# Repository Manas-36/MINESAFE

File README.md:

<div align="center">

**Integrated Worker Safety and Health Monitoring System for Mining Operations**<br>
Capstone project · B.E. Mechanical and Mechatronics Engineering · Thakur College of Engineering and Technology (TCET), Mumbai · 2026–27

</div>

MineSafe checks a miner's safety kit at the gate, watches their health and movement underground, shows where they are on a tunnel map, and lets the control room warn everyone in seconds — **without GPS, internet or cabling**.

---

## The problem

In 2024 DGMS recorded **38 fatal accidents in Indian coal mines and 32 in metalliferous mines**; fall of ground, fall of person and powered haulage lead the list. Underground there is no GPS and no mobile network. The control room cannot see a worker's condition or position, kit checks at the gate are manual, and gas, falls and heat stress are usually discovered after the fact. Existing tools each solve one piece (gas detectors, RFID gates, smart helmets, CCTV PPE detection); our [competitive analysis of nine commercial products](docs/research/competitors.md) found none that combines AI kit compliance, continuous health monitoring and GPS-free location in one underground system.

## How it works

```mermaid
flowchart LR
  B["Body unit<br>worn by miner"] -->|ESP-NOW| R3["REP-03<br>2 hops"]
  R3 -->|ESP-NOW| R2["REP-02<br>1 hop"]
  R2 -->|ESP-NOW| R1["REP-01 main<br>hop 0"]
  R1 -->|"Wi-Fi HTTP every 1 s"| H["Admin hub (laptop)<br>Flask + AI + map + gas"]
  P["Phone camera<br>entry photo"] -->|Wi-Fi| H
  E["Entry station<br>RFID gear tags"] -->|Wi-Fi| H
  H -.->|"alert in reply"| R1
  R1 -.->|beacons| R2
  R2 -.->|beacons| R3
  R3 -.->|"beacons → LED"| B
```

| Part | What it does |
|---|---|
| **Entry station** | XIAO ESP32-S3 Sense: RFID (NTAG215) tags on helmet, vest, pants, shoes + **built-in camera photo** (PHOTO button) + AI kit check (YOLOv8). Admin approves and pairs a body unit. Phone photo page as backup. |
| **Body unit** | ESP32-S3 N16R8 with MPU6050, BMP180, DS18B20, MAX30100/30102 (an ESP32-C6 + MPU6050 "mock" unit adds a second worker for demos). Steps, heading, fall, no movement, body temp, heart rate, SpO₂ (estimate), height, SOS button, alert LED. |
| **Repeater chain** | XIAO ESP32-C6 nodes along the tunnel relay data hop by hop over ESP-NOW. Routes form and heal by themselves. Each node has a buzzer and an MQ gas sensor. |
| **Control room** | `admin_hub.py` on a laptop: live status, tunnel map with worker dots, gas & air, worker registration with medical card, entry check, AI kit check, network health, incident log, one-click alert. |

### Location without GPS
Raw double integration of acceleration drifts by ~175 m in a minute, so MineSafe uses **pedestrian dead reckoning**: steps × step length along the gyro heading, kept inside the tunnels drawn on the map, and reset every time the worker passes close to a repeater. Pressure from the BMP180 gives the level (z). A built-in **Demo walker** shows the drift correction with no hardware.

### Detection rules (all editable)
| Event | Rule |
|---|---|
| Fall | free fall < 0.4 g and/or impact > 3 g, then lying > 55° after 2 s |
| No movement | no motion for 30 s (demo setting) |
| Body temperature | warning ≥ 38 °C, danger ≥ 39.5 °C |
| Heart rate | warning < 50 / > 120 bpm, danger < 40 / > 150 bpm |
| SpO₂ (estimate) | warning ≤ 92 %, danger ≤ 88 % |
| Gas | a sensor's main gas reaches its danger ppm → automatic alert to everyone |

## Progress

### Current status (5 Oct 2026)

> **V3 is in calibration — not complete yet.** The software (hub, dashboard, map, alerts, gas + air) works with the simulator and the first hardware runs. We are now integrating and calibrating the sensors one board at a time:
>
> - **Body unit on the ESP32-C6-WROOM-1 DevKit** — own pin map in `body_node`; sensors checked with [`firmware/tests/body_sensor_test`](firmware/tests/body_sensor_test) (wire check + pin finder). Currently fixing the I²C / DS18B20 wiring.
> - **Scanning system (entry station) on an ESP32-C6** — PN532 RFID antenna + OLED + buttons, checked with [`firmware/tests/entry_hw_test`](firmware/tests/entry_hw_test); entry photo from the phone page. (The XIAO S3 Sense camera build is kept as an option.)
> - **Sensor code cross-checked** against the standard libraries and datasheets; [`firmware/tests/body_lib_test`](firmware/tests/body_lib_test) reads every body sensor with the well-known Arduino libraries.
> - **Repeaters (XIAO ESP32-C6)** — chain, buzzer, MQ gas and AHT air sensor working on the bench (31.3 °C / 62 % RH).
>
> **V4 — our own PCBs and sensor boards.** Once V3 is calibrated, the breadboard wiring is replaced by custom-designed PCBs: a compact body-unit board with the sensors on it, a repeater board and an entry-station board — see [docs/v4.md](docs/v4.md).

**Major versions:** [V1](docs/v1.md) Wi-Fi + cloud, no website → [V2](docs/v2.md) ESP-NOW chain + control-room website → **[V3](docs/v3.md) camera entry station + sensor integration (now, calibrating)** → **[V4](docs/v4.md) our own PCBs and sensor boards**

**42 / 59 tasks done · Week 9 of 14** `████████████████████░░░░░░░░░░` → full week-by-week plan, Gantt chart and checklist in **[ROADMAP.md](ROADMAP.md)**

| Version | Milestone | Status |
|---|---|---|
| v0.0 | Research, competitive analysis, architecture, pilot BOM | ✅ |
| v0.1 | Entry station reads / writes gear tags; tag registry | ✅ |
| v0.2 | Phone photo verification, body-unit clearance | ✅ |
| v0.3 | Control room v3: workers, live monitoring, alerts; entry station v2 | ✅ |
| v0.4 | Repeater chain, AI kit check, gas; Zigbee → ESP-NOW | ✅ |
| v0.5 | First end-to-end run: phone worker, body unit, alerts, buzzer | ✅ tested on hardware |
| v0.6 | Tunnel map + GPS-free tracking, gas analysis, real body sensors | ✅ software · 🔧 sensor bench test next |
| v1.0 | Structured repo, docs, presentation, Notion | ✅ |
| **V3 · v3.0** | Camera entry station (XIAO S3 Sense), mock worker, schematics, admin theme, research docs — [docs/v3.md](docs/v3.md) | ✅ software · 🔧 hardware test next |
| v3.1 | AHT air temperature + humidity on every repeater, shown in the admin with wet-bulb heat warnings | ✅ software · 🔧 hardware test next |
| v3.2 | Body unit on ESP32-C6-WROOM-1 DevKit, sensor + entry hardware test sketches, serial on both USB sockets | 🔧 calibrating sensors |
| v3.3 | Repeater exit sign (LED matrix) + evacuation routes to the nearest safe exit, 3 gas sensors per repeater, editable gas limits (CMR 2017 / NIOSH) — [gas limits](docs/gas_limits.md) · [final BOM](docs/final_bom.md) · [run guide](docs/run_on_laptop.md) | ✅ software · 🔧 hardware next |
| **V4** | Custom PCBs: body-unit sensor board, repeater board, entry-station board — [docs/v4.md](docs/v4.md) | 📋 planned |

Every version has its own branch (`version/v0.0` … `version/v1.0`) — see [CHANGELOG.md](CHANGELOG.md) for what changed and [docs/decisions.md](docs/decisions.md) for why.

## Repository layout

```
firmware/
  body_node/          body unit (worn)            – ESP32-S3 or XIAO ESP32-C6
  repeater_node/      main + tunnel repeaters     – set IS_GATEWAY / REPEATER_NO
  entry_station/      RFID gear tag station        – XIAO ESP32-C6 + PN532 + OLED
  tests/              i2c_scan, rc522_test, pn532_ntag215_test
hub/
  admin_hub.py        control room server + dashboard (Flask)
  requirements.txt
tools/
  sim_repeater.py     fake repeater chain + 3 workers (no hardware)
  mock_repeater.py    serves the repeater's phone test page on a PC
hardware/
  bom_prototype.csv   parts for the built prototype
  bom_pilot.csv       parts for the 20-worker pilot design
docs/
  v1.md v2.md v3.md  architecture.md  wiring.md  setup.md  protocol.md  decisions.md
  wiring/             schematics (SVG + PNG) and the script that draws them
  research/           literature review, competitor analysis, pilot design, original reports (source/)
  presentation/       slide outline (add the exported PDF here)
  images/             screenshots
CHANGELOG.md          version-by-version progress
ROADMAP.md            week-by-week plan and to-do list
```

## Quick start

1. **Hub (laptop)**
   ```bash
   cd hub
   pip install -r requirements.txt     # ultralytics is optional (AI kit check)
   python admin_hub.py                 # open http://localhost:5000
   ```
   No hardware yet? Run `python tools/sim_repeater.py` in a second window, or press **▶ Demo walker** on the Map tab.
2. **Firmware (Arduino IDE, ESP32 core 3.x)**
   - Copy `secrets.example.h` → `secrets.h` in `repeater_node/` and `entry_station/`, fill in your hotspot and laptop IP.
   - Board: *ESP32S3 Dev Module* or *XIAO_ESP32C6*, USB CDC On Boot: Enabled, Serial Monitor 115200.
   - Main repeater: `IS_GATEWAY 1`, `REPEATER_NO 1`. Tunnel repeaters: `IS_GATEWAY 0`, numbers 2, 3, 4 …
   - Body unit: set `BODY_ID`, stand still 3 s at power-on.
3. **Test with a phone:** join the hotspot, open `http://<repeater IP>/` — the phone acts as a worker (fall, SOS, walk on the map).

Full steps: [docs/setup.md](docs/setup.md) · Wiring + schematics: [docs/wiring.md](docs/wiring.md) · Packet format: [docs/protocol.md](docs/protocol.md) · Architecture: [docs/architecture.md](docs/architecture.md)

## Screenshots

**New (v3.5): MineSafe Control** — a 3D control-room app at `http://<laptop-ip>:5000/control/`, live data only, works on a phone: **[docs/control_app.md](docs/control_app.md)**.

Every page of the classic control-room website: **[docs/website.md](docs/website.md)**. Reports: **[docs/report](docs/report/)** (blue book + figures).

| Evacuation map | Live |
|---|---|
|  |  |
| **Gas limits** | **Body unit display (v3.4)** |
|  |  |

*Screens from a test run with the demo mine map, the repeater simulator and fictional demo workers.*

## Bill of materials

| Build | Cost |
|---|---|
| Prototype (1 body unit, 2 repeaters, entry station; laptop + phone owned) | ≈ ₹6,500 |
| Pilot design (20 workers, 2 entry chambers, 8 UWB/LoRa repeaters, gateway, server) | ≈ ₹3,01,000 |

Approximate India-market prices, 2026. Item-by-item: [hardware/bom_prototype.csv](hardware/bom_prototype.csv) · [hardware/bom_pilot.csv](hardware/bom_pilot.csv).

## Future scope
Zigbee (802.15.4) mesh on ESP32-C6 nodes · UWB anchors for sub-metre location · LoRa backbone for long tunnels · MQ-4 / electrochemical CO and O₂ sensors · intrinsically safe enclosure · kit-removal sensing (helmet IR sensor, vest buckle reed switch, BLE tags) · OLED messages to workers · shift analytics.

## Team
| Name | Roll no. | GitHub |
|---|---|---|
| Manas Pednekar | 36 | [@Manas-36](https://github.com/Manas-36) |
| Amey Satale | 46 | [@Ameyty](https://github.com/Ameyty) |
| Aaryaa Kanojia | 18 | [@aaryaakanojia21](https://github.com/aaryaakanojia21) |

Guide: **Mr Dipesh Tare**, Assistant Professor · Full credits: [CONTRIBUTORS.md](CONTRIBUTORS.md)

## Licence
MIT — see [LICENSE](LICENSE).

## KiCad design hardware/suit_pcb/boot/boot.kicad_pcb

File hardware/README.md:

# MineSafe hardware — repeater PCB v4.0 and case

> V4 smart suit pods (4 PCBs + enclosures + full-suit CAD): see **[suit.md](suit.md)**.

This replaces the breadboard / jumper-wire repeater with **one carrier PCB** for the Seeed XIAO ESP32-C6 and a **mine-rated enclosure** designed around it. It uses the same pins as `firmware/repeater_node` (v3.3), so the firmware runs unchanged. Set `GAS_CHANNELS 3` to use all three gas inputs.

| | |
|---|---|
|  |  |
|  |  |

## What a repeater has to survive underground — and how the design answers it
| Mine condition | Design answer |
|---|---|
| **Water**: roof drips, wet walls, hosing-down, humidity up to 100 % | Sealed base and lid: a 3 mm silicone cord in a groove on a 9 mm land, with a tongue on the lid that presses it (aim **IP65**). A **drip hood** over the window. Every opening that could collect water faces **down**: the power gland, the pressure vent, and the CO and H₂S ports. The side vent of the AHT20 chamber sits under a drip lip. Conformal-coat the PCB after testing. |
| **Dust** (coal and rock dust) | Same seal. Every sensor breathes only through a **sintered-bronze disc and an ePTFE membrane**, never through open holes. |
| **Methane, which is lighter than air**, collects at the roof | The **MQ-4 (CH₄)** port is in the **top** wall. It sits under a "chimney" with side windows, so gas gets in but drips cannot fall onto the membrane. |
| **H₂S, which is heavier than air**, and CO | The **MQ-136 (H₂S)** and **MQ-7 (CO)** ports are in the **bottom** wall. Short skirts protect them from knocks. |
| **Gas ignition risk** (hot MQ heaters, sparks) | Each sensor port has a seat for a **sintered flame-arrestor disc**. The sensor board screws onto a foam gasket, so the heater only "sees" the outside through that disc. ⚠ A real coal-mine product still needs intrinsic-safety design and certification (Ex ia / Ex d). This case is a capstone prototype and is **not certified**. |
| **Heat** (30–45 °C) plus the MQ heaters (≈ 0.75 W each) | The **AHT20 sits in its own walled chamber** in the bottom-left corner. It has its own vent, far from the heaters, so it measures the tunnel air and not the box. A switching regulator (K7805, ≈ 90 % efficient) replaces a hot linear 7805. |
| **Blasting shock and vibration** | All boards are on screw bosses, with no hot glue and no breadboard. The XIAO and the 74HCT125 sit in sockets with a cable-tie. JST-XH latching connectors are used throughout. The lid lugs have gussets, and the mounting tabs have ribs. Fit **rubber grommets** in the 16 mm mounting holes. |
| **Falling rock, knocks from machines** | 3.5–4 mm walls in PC-ABS FR. The window is **3 mm polycarbonate** set in a recess behind a raised bezel. The SOS button has a **guard ring** with finger gaps, so a passing load cannot press it but a gloved hand can. |
| **Mine power cuts** | Two inputs: **MAIN 9–30 V** (mine supply) and **BATT 12 V** (3S 18650 pack with BMS). They are joined through Schottky diodes, so the board switches to battery with no reset. A **mains-present signal** (Q2 → D7) lets the firmware report "running on battery". On the input: a 1.6 A slow fuse, a 36 V TVS and a 470 µF capacitor. |
| **Radio in a rock tunnel** | The XIAO's u.FL connector goes through a pigtail to an **SMA bulkhead on the top wall**, so the antenna sits outside the box and clear of the rock face. |
| **Visibility in smoke and darkness** | The LED-matrix exit sign is under the hood, at eye level when the box is mounted on the rib. Two recesses take **reflective hi-vis tape**, which shows up in cap-lamp light. A power LED shows through a light pipe. |
| **Mounting** on the rib, a rock-bolt plate, roof mesh or a chain | Top and bottom tabs with a 16 mm hole (grommet, bolt or hook) and two slots each. Hang the box with the top tab only from roof mesh, or bolt both tabs to the rib. |
| **Static electricity** | Use antistatic FR plastic. An **earth stud boss** inside bonds the box to the mine earth. |
| **Pressure and temperature swings** (ventilation fans, depth) | An M12 **ePTFE pressure vent** in the bottom wall stops the seal from "breathing" water in. |

## Wiring the prototype

Every cable from the PCB connectors to the parts in the case, pin by pin, with lengths and wire colours. Generated by `docs/wiring/make_repeater_v4_wiring.py`. Shopping list for two repeaters: [`repeater_x2_shopping_list.xlsx`](repeater_x2_shopping_list.xlsx).

## PCB — `repeater_pcb/`
- **Board**: 100 × 75 mm, 2 layers, 1.6 mm, ground pour on both layers. Every part is through-hole, so the team can hand-solder it. 4 × M3 holes, 3.5 mm in from each corner.
- **Circuit**: [schematic](repeater_pcb/renders/repeater_schematic.png).
  - **Power**: OR diodes → fuse → TVS → K7805-2000R3 (5 V / 2 A).
  - **Controller**: XIAO ESP32-C6 on sockets.
  - **Matrix driver**: a 74HCT125 lifts the 3.3 V signals to 5 V for the MAX7219.
  - **Gas inputs**: three MQ inputs, each with a 10 k / 20 k divider and a filter capacitor.
  - **Other parts**: buzzer driver (S8050 + flyback diode), SOS input with debounce, AHT20 header with I²C pull-ups.
- **Connectors**:
  - power terminals on the left;
  - MQ1–3 at the bottom;
  - matrix, buzzer, SOS and AHT20 on the right;
  - USB-C at the top for programming.
- **Routing**: autorouted with Freerouting. Power tracks are 0.8 mm, signal tracks 0.3 mm, clearance 0.25 mm. DRC shows 0 unconnected pads. The remaining DRC items are only silkscreen cosmetics and "footprint library not found" (no KiCad library table on the build machine).
- **Source files**: `build_board.py` generates the whole board (placement, netlist, DSN for Freerouting, SES import, zones and silkscreen). `repeater.kicad_pcb` / `.kicad_pro` open in KiCad 7+.
- **Parts list**: [`bom_pcb.csv`](repeater_pcb/bom_pcb.csv), about **₹730 per board** of parts plus about ₹60 for the bare PCB.

### Ordering the PCB (JLCPCB / PCBWay)
1. Upload `repeater_pcb/repeater_gerbers_jlcpcb.zip`.
2. Use the defaults: 2 layers, 1.6 mm, HASL (lead-free if you like), any colour. 5 boards cost about USD 2 plus shipping.
3. No assembly is needed. Solder the low parts first (resistors, diodes), then the sockets, connectors and capacitors.
4. Before fitting the XIAO, power J1 from 12 V. Check for 5.0 V at the U2B "5V" pin and 0 V between the XIAO pins. Then fit the XIAO.

## Case — `repeater_case/`
- **Two parts**: the **base**, which bolts to the wall and carries everything, and the **lid** (window, SOS button, buzzer grille, hood).
- **Outside size**: 223 × 292 × 118 mm, including the mounting tabs and the hood. The body alone is 198 × 228 × 84 mm.
- **Lid fixing**: 6 × M4 stainless screws into heat-set inserts in the base.
- **Files**:
  - `case_base.step/.stl`, `case_lid.step/.stl`;
  - `case_assembly.step`, which includes the PCB, matrix, sensors, battery and button as blocks for the fit check;
  - `build_case.py` (CadQuery), where every dimension is a named constant at the top.
- **Fit check**: `fit_report.txt`. The PCB, matrix, window, 3 MQ modules, AHT20, battery, charger, SOS button, buzzer, gland nut and vent nut clear the case and each other.

**Layout, front view with the lid off:**

| Zone | What sits there |
|---|---|
| Top wall | CH₄ chimney (right), SMA antenna (left) |
| Top of the lid | LED matrix behind the window, under the hood |
| Middle | PCB on 12 mm standoffs. Leave a USB-C service loop at the top. |
| Bottom row | AHT20 chamber with side vent · M16 power gland · battery bay (3S 18650 pack, BMS, charge module, strap slots) · CO and H₂S modules over their ports |
| Front of the lid, lower part | Buzzer grille · power LED · guarded 22 mm SOS button |

**Printing / making:**
- **Prototype**: FDM in **PETG or ASA**, 4 perimeters, 30 % infill. Print the base back-down and the lid face-down. You will need supports under the hood and the lugs.
- **Real use underground**: **PC-ABS FR, V-0 and antistatic** (surface resistance below 10⁹ Ω), injection-moulded or SLS-printed. Ordinary PLA softens at mine temperatures and is not flame-retardant.
- **Window**: 145 × 49 × 3 mm polycarbonate, laser-cut. Seal it with a 1 mm EPDM foam gasket or a bead of neutral-cure silicone.

### Extra parts for the case
| Part | Qty | ≈ ₹ |
|---|---|---|
| Silicone cord 3 mm (gasket), 1 m | 1 | 60 |
| M4 × 25 stainless screws + M4 heat-set inserts | 6 | 90 |
| M16 cable gland IP68 (for 6–10 mm cable) | 1 | 40 |
| M12 ePTFE pressure vent (screw-in) | 2 (bottom + AHT20 chamber) | 200 |
| Sintered bronze disc 25 mm × 3 mm (flame arrestor) | 3 | 180 |
| ePTFE membrane patches 25 mm (or cut from a vent sticker) | 4 | 120 |
| 22 mm IP67 mushroom push button (red, NO) | 1 | 150 |
| SMA bulkhead pigtail (u.FL → SMA female) + 2.4 GHz antenna | 1 | 250 |
| Polycarbonate sheet 3 mm, 150 × 50 | 1 | 60 |
| 3S 18650 pack with BMS (3 × 18650) + 12.6 V CC/CV buck-boost charge module | 1 | 900 |
| Reflective hi-vis tape 12 mm, 0.5 m | 1 | 50 |
| Rubber grommets 16 mm + M3 screws | — | 50 |
| Printing (PETG, ≈ 1.1 kg with supports) | — | 1,000 |
| **Case total** | | **≈ ₹3,150** |

With the PCB (≈ ₹790) and the modules already listed in [`docs/final_bom.md`](../docs/final_bom.md) (XIAO, matrix, MQ sensors, AHT20, buzzer), a complete repeater comes to about **₹6,000**.

## To do
- **Firmware**: read `MAINS_N` on D7 (GPIO17); LOW means mine supply present. Send an "on battery" flag in the status packet and show it on the hub and the 3D control app.
- **Battery charging**: the board does not charge the battery itself. The charge module in the battery bay takes VIN_MAIN and charges the 3S pack at 12.6 V CC/CV. Choose a buck-boost module so that it also works from a 12 V mine supply.
- **Before going underground**: water test (hose, 30 min), drop / impact test, and a 24 h run at 45 °C.

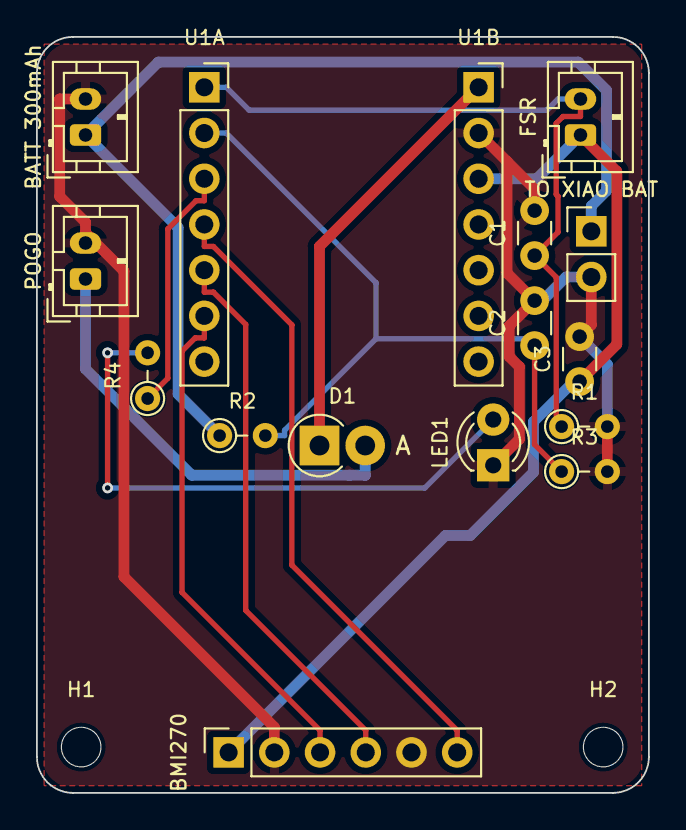
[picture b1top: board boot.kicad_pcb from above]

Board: 2 copper layers, 34.0 x 42.0 mm, 18 parts (0 on the bottom side), 12 nets.

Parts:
C1, C2, C3: 100nF; C_Disc_D3.0mm_W1.6mm_P2.50mm
D1: 1N5819; D_DO-41_SOD81_P2.54mm_Vertical_AnodeUp
H1, H2: M2; MountingHole_2.2mm_M2
J1: BATT 300mAh; JST_PH_B2B-PH-K_1x02_P2.00mm_Vertical
J2: POGO; JST_PH_B2B-PH-K_1x02_P2.00mm_Vertical
J3: FSR; JST_PH_B2B-PH-K_1x02_P2.00mm_Vertical
J4: TO XIAO BAT; PinHeader_1x02_P2.54mm_Vertical
LED1: STATUS; LED_D3.0mm
R1: 10k; R_Axial_DIN0204_L3.6mm_D1.6mm_P2.54mm_Vertical
R2, R3: 220k; R_Axial_DIN0204_L3.6mm_D1.6mm_P2.54mm_Vertical
R4: 1k; R_Axial_DIN0204_L3.6mm_D1.6mm_P2.54mm_Vertical
U1A: XIAO D0-D6; PinSocket_1x07_P2.54mm_Vertical
U1B: XIAO 5V-D7; PinSocket_1x07_P2.54mm_Vertical
U2: BMI270; PinSocket_1x06_P2.54mm_Vertical

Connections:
+3V3: C3.1, J3.1, U1B.3, U2.1
+5V: D1.1, U1B.1
BAT+: J1.1, J4.1, R2.1
FSR: C1.1, J3.2, R1.1, U1A.1
GND: C1.2, C2.2, C3.2, J1.2, J2.2, J4.2, LED1.1, R1.2, R3.2, U1B.2, U2.2, U2.5
IMU_INT: U1A.4, U2.6
LED: R4.1, U1A.3
LED_A: LED1.2, R4.2
POGO+: D1.2, J2.1
SCL: U1A.6, U2.3
SDA: U1A.5, U2.4
VBAT_SNS: C2.1, R2.2, R3.1, U1A.2

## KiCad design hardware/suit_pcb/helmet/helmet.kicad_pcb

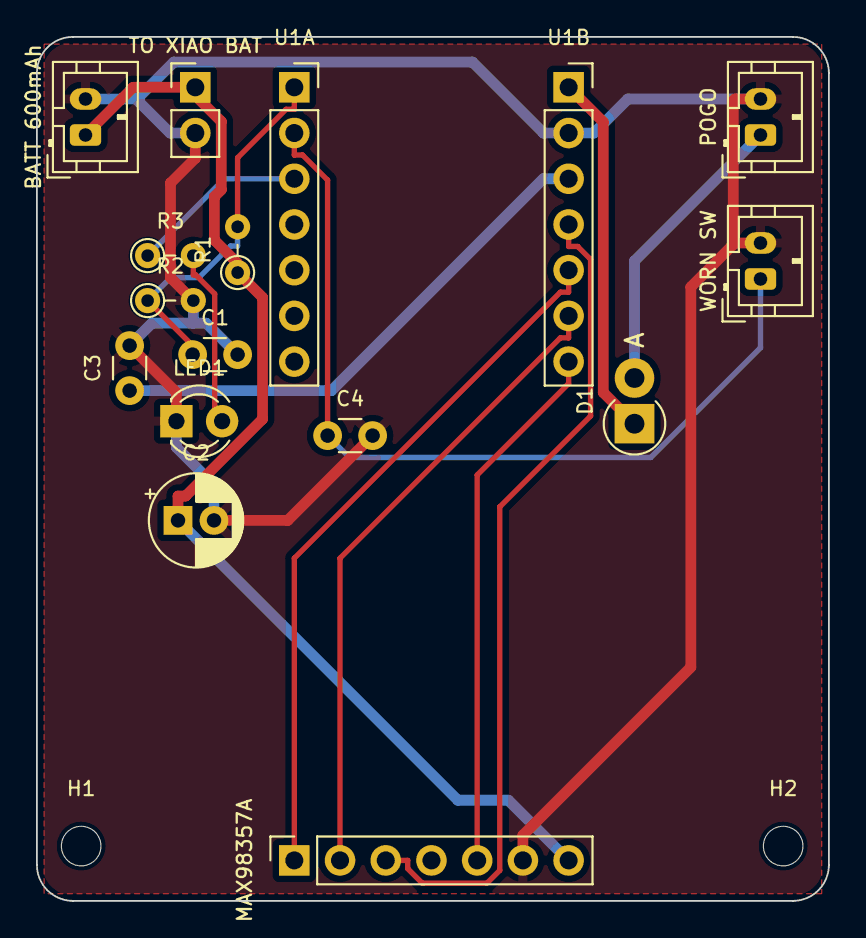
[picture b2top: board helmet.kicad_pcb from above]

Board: 2 copper layers, 44.0 x 48.0 mm, 18 parts (0 on the bottom side), 13 nets.

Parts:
C1, C3, C4: 100nF; C_Disc_D3.0mm_W1.6mm_P2.50mm
C2: 100uF 10V; CP_Radial_D5.0mm_P2.00mm
D1: 1N5819; D_DO-41_SOD81_P2.54mm_Vertical_AnodeUp
H1, H2: M2; MountingHole_2.2mm_M2
J1: BATT 600mAh; JST_PH_B2B-PH-K_1x02_P2.00mm_Vertical
J2: TO XIAO BAT; PinHeader_1x02_P2.54mm_Vertical
J3: POGO; JST_PH_B2B-PH-K_1x02_P2.00mm_Vertical
J4: WORN SW; JST_PH_B2B-PH-K_1x02_P2.00mm_Vertical
LED1: STATUS; LED_D3.0mm
R1, R2: 220k; R_Axial_DIN0204_L3.6mm_D1.6mm_P2.54mm_Vertical
R3: 1k; R_Axial_DIN0204_L3.6mm_D1.6mm_P2.54mm_Vertical
U1A: XIAO D0-D6; PinSocket_1x07_P2.54mm_Vertical
U1B: XIAO 5V-D7; PinSocket_1x07_P2.54mm_Vertical
U2: MAX98357A; PinSocket_1x07_P2.54mm_Vertical

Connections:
+3V3: C3.1, U1B.3
+5V: D1.1, U1B.1
AMP_SD: U1B.7, U2.5
BAT+: C2.1, J1.1, J2.1, R1.1, U2.7
GND: C1.2, C2.2, C3.2, C4.2, J1.2, J2.2, J3.2, J4.2, LED1.1, R2.2, U1B.2, U2.6
I2S_BCLK: U1B.6, U2.2
I2S_DIN: U1B.4, U2.3
I2S_LRC: U1B.5, U2.1
LED: R3.1, U1A.3
LED_A: LED1.2, R3.2
POGO+: D1.2, J3.1
VBAT_SNS: C1.1, R1.2, R2.1, U1A.1
WORN: C4.1, J4.1, U1A.2

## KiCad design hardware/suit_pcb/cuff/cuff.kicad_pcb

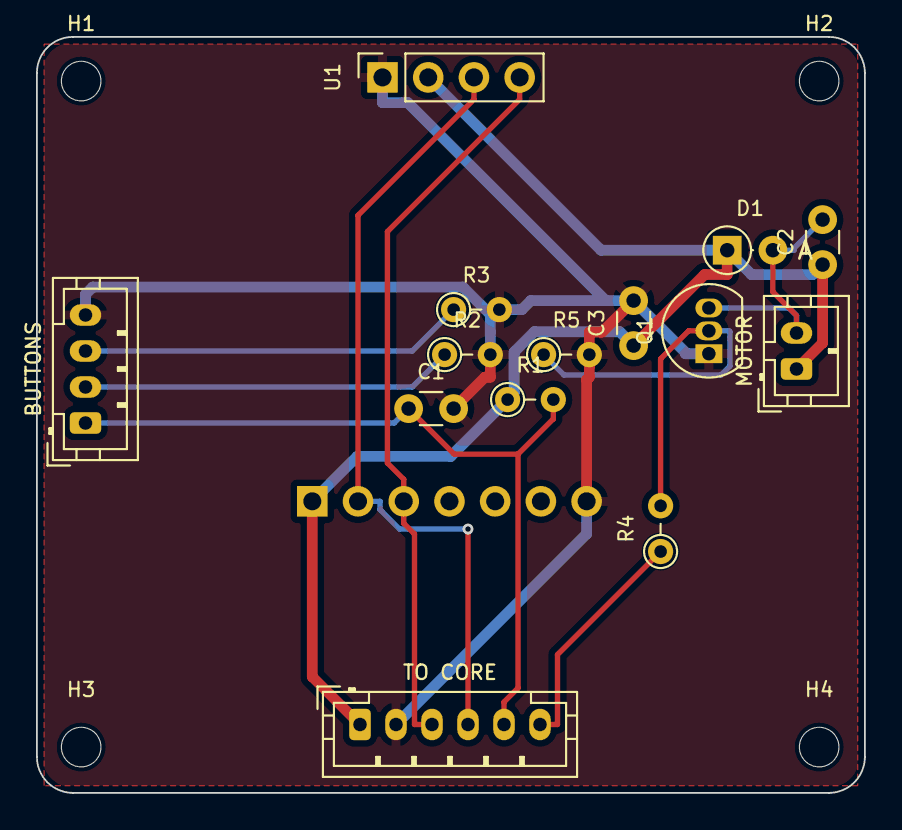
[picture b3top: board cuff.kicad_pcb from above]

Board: 2 copper layers, 46.0 x 42.0 mm, 19 parts (1 on the bottom side), 10 nets.

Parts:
C1, C2, C3: 100nF; C_Disc_D3.0mm_W1.6mm_P2.50mm
D1: 1N4148; D_DO-35_SOD27_P2.54mm_Vertical_AnodeUp
H1, H2, H3, H4: M2; MountingHole_2.2mm_M2
J1: TO CORE; JST_PH_B6B-PH-K_1x06_P2.00mm_Vertical
J2: BUTTONS; JST_PH_B4B-PH-K_1x04_P2.00mm_Vertical
J3: MOTOR; JST_PH_B2B-PH-K_1x02_P2.00mm_Vertical
Q1: S8050; TO-92_Inline
R1, R5: 10k; R_Axial_DIN0204_L3.6mm_D1.6mm_P2.54mm_Vertical
R2: 2.2k; R_Axial_DIN0204_L3.6mm_D1.6mm_P2.54mm_Vertical
R3: 6.8k; R_Axial_DIN0204_L3.6mm_D1.6mm_P2.54mm_Vertical
R4: 1k; R_Axial_DIN0204_L3.6mm_D1.6mm_P2.54mm_Vertical
U1: OLED 1.3in; PinSocket_1x04_P2.54mm_Vertical
U2: MAX30102; PinSocket_1x07_P2.54mm_Vertical

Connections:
+3V3: C2.1, C3.1, D1.1, J1.1, J3.1, R1.1, U1.2, U2.1
BTN: C1.1, J1.5, J2.1, R1.2
GND: C1.2, C3.2, J1.2, J2.4, Q1.1, R2.2, R3.2, R5.2, U1.1, U2.7
HAPTIC: J1.6, R4.1
MENU_R: J2.3, R3.1
MOT_N: C2.2, D1.2, J3.2, Q1.3
OK_R: J2.2, R2.1
Q_B: Q1.2, R4.2, R5.1
SCL: J1.4, U1.3, U2.2
SDA: J1.3, U1.4, U2.3

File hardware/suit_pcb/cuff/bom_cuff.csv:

Qty,References,Value / module,Footprint,Description,Approx INR each
3,C1 C2 C3,100nF,C_Disc_D3.0mm_W1.6mm_P2.50mm,ceramic capacitor,1
1,D1,1N4148,D_DO-35_SOD27_P2.54mm_Vertical_AnodeUp,signal diode,1
1,J1,TO CORE,JST_PH_B6B-PH-K_1x06_P2.00mm_Vertical,JST-PH 2.0 mm vertical + housing + crimped lead,8
1,J2,BUTTONS,JST_PH_B4B-PH-K_1x04_P2.00mm_Vertical,JST-PH 2.0 mm vertical + housing + crimped lead,8
1,J3,MOTOR,JST_PH_B2B-PH-K_1x02_P2.00mm_Vertical,JST-PH 2.0 mm vertical + housing + crimped lead,8
1,Q1,S8050,TO-92_Inline,NPN transistor,2
2,R1 R5,10k,R_Axial_DIN0204_L3.6mm_D1.6mm_P2.54mm_Vertical,"resistor 1/8 W, standing",0.5
1,R2,2.2k,R_Axial_DIN0204_L3.6mm_D1.6mm_P2.54mm_Vertical,"resistor 1/8 W, standing",0.5
1,R3,6.8k,R_Axial_DIN0204_L3.6mm_D1.6mm_P2.54mm_Vertical,"resistor 1/8 W, standing",0.5
1,R4,1k,R_Axial_DIN0204_L3.6mm_D1.6mm_P2.54mm_Vertical,"resistor 1/8 W, standing",0.5
1,U1,OLED 1.3in,PinSocket_1x04_P2.54mm_Vertical,female header socket 2.54 mm,10
1,U2,MAX30102,PinSocket_1x07_P2.54mm_Vertical,female header socket 2.54 mm,10
1,PCB,MineSafe cuff v4.0,2-layer 1.6 mm,JLCPCB (5 pcs min),50

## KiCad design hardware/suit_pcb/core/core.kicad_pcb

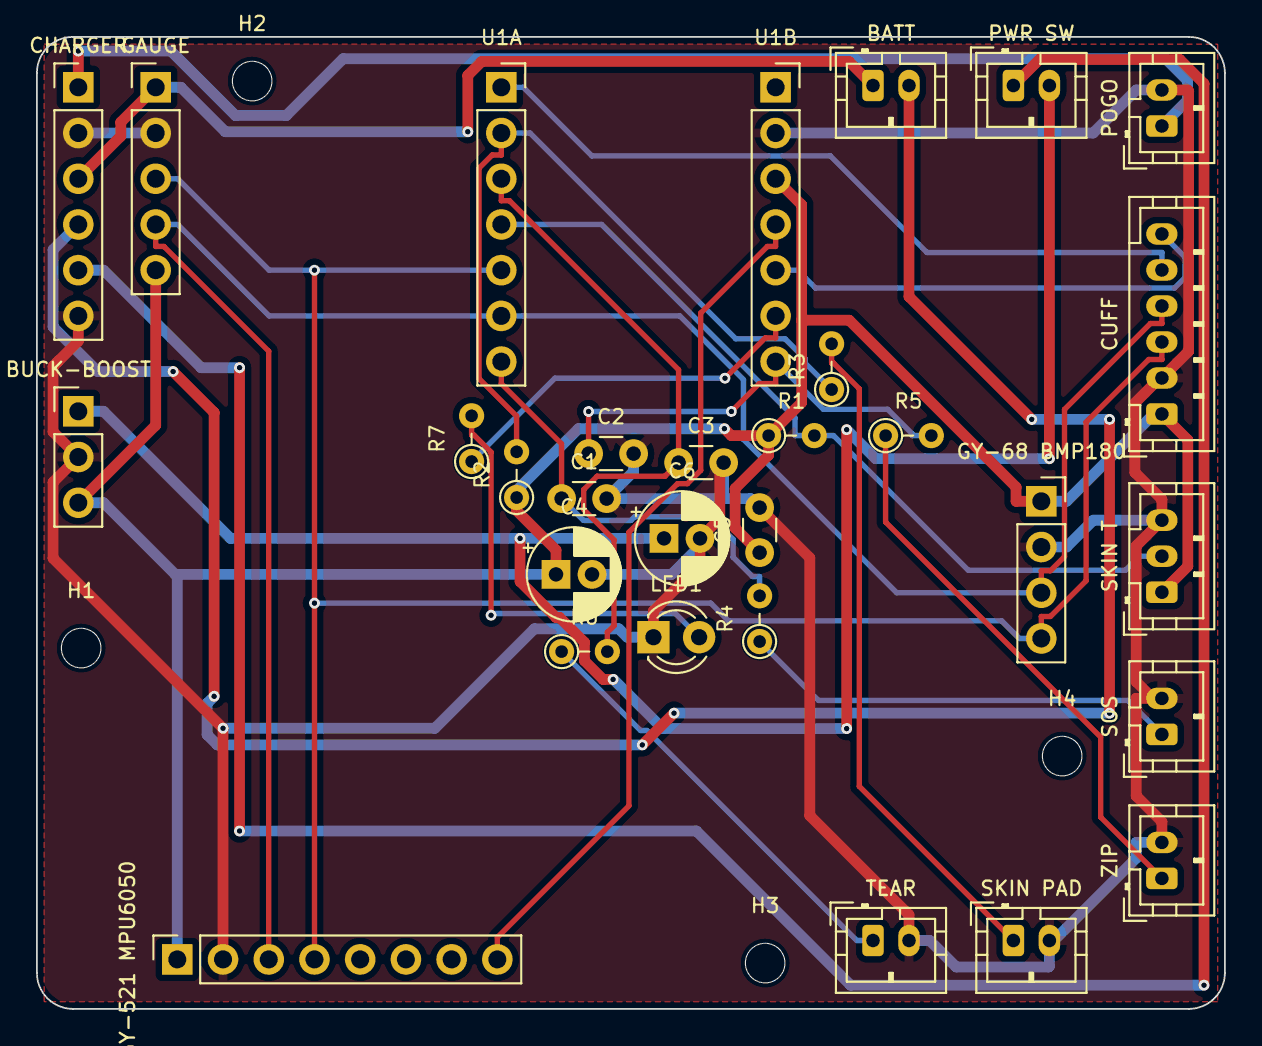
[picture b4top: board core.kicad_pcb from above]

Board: 2 copper layers, 66.0 x 54.0 mm, 34 parts (0 on the bottom side), 23 nets.

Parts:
C1, C2, C3, C5: 100nF; C_Disc_D3.0mm_W1.6mm_P2.50mm
C4, C6: 100uF 10V; CP_Radial_D5.0mm_P2.00mm
H1, H2, H3, H4: M2; MountingHole_2.2mm_M2
J1: BATT; JST_PH_B2B-PH-K_1x02_P2.00mm_Vertical
J2: PWR SW; JST_PH_B2B-PH-K_1x02_P2.00mm_Vertical
J3: POGO; JST_PH_B2B-PH-K_1x02_P2.00mm_Vertical
J4: CUFF; JST_PH_B6B-PH-K_1x06_P2.00mm_Vertical
J5: SKIN T; JST_PH_B3B-PH-K_1x03_P2.00mm_Vertical
J6: SOS; JST_PH_B2B-PH-K_1x02_P2.00mm_Vertical
J7: ZIP; JST_PH_B2B-PH-K_1x02_P2.00mm_Vertical
J8: TEAR; JST_PH_B2B-PH-K_1x02_P2.00mm_Vertical
J9: SKIN PAD; JST_PH_B2B-PH-K_1x02_P2.00mm_Vertical
J10: CHARGER; PinHeader_1x06_P2.54mm_Vertical
J11: BUCK-BOOST; PinHeader_1x03_P2.54mm_Vertical
J12: GAUGE; PinHeader_1x05_P2.54mm_Vertical
LED1: STATUS; LED_D3.0mm
R1: 4.7k; R_Axial_DIN0204_L3.6mm_D1.6mm_P2.54mm_Vertical
R2: 1M; R_Axial_DIN0204_L3.6mm_D1.6mm_P2.54mm_Vertical
R3: 470; R_Axial_DIN0204_L3.6mm_D1.6mm_P2.54mm_Vertical
R4, R5, R6, R7: 1k; R_Axial_DIN0204_L3.6mm_D1.6mm_P2.54mm_Vertical
U1A: XIAO D0-D6; PinSocket_1x07_P2.54mm_Vertical
U1B: XIAO 5V-D7; PinSocket_1x07_P2.54mm_Vertical
U2: GY-521 MPU6050; PinSocket_1x08_P2.54mm_Vertical
U3: GY-68 BMP180; PinSocket_1x04_P2.54mm_Vertical

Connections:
+3V3: C4.1, C5.1, J4.1, J5.1, J11.3, J12.5, R1.1, R2.1, U1B.3, U2.1, U3.1
BAT+: J1.1, J10.3, J12.1
BAT_N: J1.2, J10.4
BTN: J4.5, U1A.1
CHG_OUT: J2.1, J10.5
GND: C1.2, C2.2, C3.2, C4.2, C5.2, C6.2, J3.2, J4.2, J5.3, J6.2, J7.2, J8.2, J9.2, J10.2, J10.6, J11.2, J12.2, LED1.1, U1B.2, U2.2, U3.2
HAPTIC: J4.6, U1B.5
IMU_INT: U1B.4, U2.8
LED: R7.1, U1B.6
LED_A: LED1.2, R7.2
ONEWIRE: J5.2, R1.2, U1A.4
POGO+: J3.1, J10.1
SCL: J4.4, J12.4, U1A.6, U2.3, U3.3
SDA: J4.3, J12.3, U1A.5, U2.4, U3.4
SKIN: R2.2, R3.1, U1A.2
SKIN_PAD: J9.1, R3.2
SOS: C1.1, R4.2, U1A.7
SOS_RAW: J6.1, R4.1
TEAR: C3.1, R6.2, U1A.3
TEAR_RAW: J8.1, R6.1
VSYS: C6.1, J2.2, J11.1
ZIP: C2.1, R5.2, U1B.7
ZIP_RAW: J7.1, R5.1

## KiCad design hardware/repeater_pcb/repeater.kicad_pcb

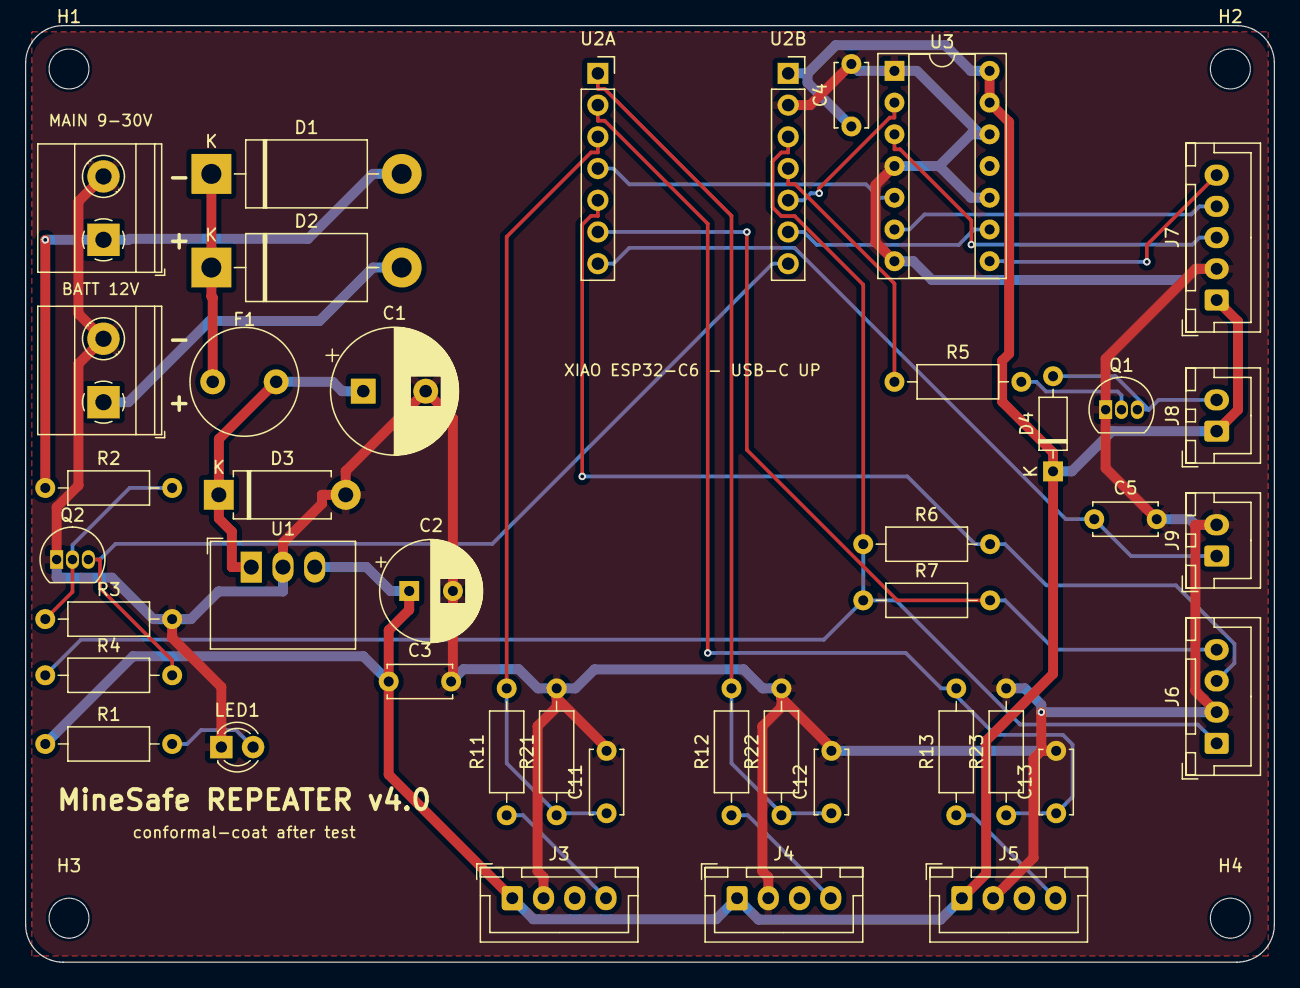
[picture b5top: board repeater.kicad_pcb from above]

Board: 2 copper layers, 100.0 x 75.0 mm, 46 parts (0 on the bottom side), 28 nets.

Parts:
C1: 470uF 50V; CP_Radial_D10.0mm_P5.00mm
C2: 220uF 16V; CP_Radial_D8.0mm_P3.50mm
C3, C4, C5, C11, C12, C13: 100nF; C_Disc_D5.0mm_W2.5mm_P5.00mm
D1, D2: 1N5822; D_DO-201AD_P15.24mm_Horizontal
D3: P6KE36A; D_DO-15_P10.16mm_Horizontal
D4: 1N4148; D_DO-35_SOD27_P7.62mm_Horizontal
F1: T1.6A TR5; Fuse_Littelfuse_372_D8.50mm
H1, H2, H3, H4: M3; MountingHole_3.2mm_M3
J1: MAIN 9-30V; TerminalBlock_Phoenix_MKDS-1,5-2-5.08_1x02_P5.08mm_Horizont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
J2: BATT 12V; TerminalBlock_Phoenix_MKDS-1,5-2-5.08_1x02_P5.08mm_Horizont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
J3: MQ1; JST_XH_B4B-XH-A_1x04_P2.50mm_Vertical
J4: MQ2; JST_XH_B4B-XH-A_1x04_P2.50mm_Vertical
J5: MQ3; JST_XH_B4B-XH-A_1x04_P2.50mm_Vertical
J6: AHT20; JST_XH_B4B-XH-A_1x04_P2.50mm_Vertical
J7: MATRIX; JST_XH_B5B-XH-A_1x05_P2.50mm_Vertical
J8: BUZZER; JST_XH_B2B-XH-A_1x02_P2.50mm_Vertical
J9: SOS; JST_XH_B2B-XH-A_1x02_P2.50mm_Vertical
LED1: PWR; LED_D3.0mm
Q1, Q2: S8050; TO-92_Inline
R1, R5: 1k; R_Axial_DIN0207_L6.3mm_D2.5mm_P10.16mm_Horizontal
R2: 22k; R_Axial_DIN0207_L6.3mm_D2.5mm_P10.16mm_Horizontal
R3, R4, R11, R12, R13: 10k; R_Axial_DIN0207_L6.3mm_D2.5mm_P10.16mm_Horizontal
R6, R7: 4.7k; R_Axial_DIN0207_L6.3mm_D2.5mm_P10.16mm_Horizontal
R21, R22, R23: 20k; R_Axial_DIN0207_L6.3mm_D2.5mm_P10.16mm_Horizontal
U1: K7805-2000R3; Converter_DCDC_RECOM_R-78B-2.0_THT
U2A: XIAO D0-D6; PinSocket_1x07_P2.54mm_Vertical
U2B: XIAO 5V-D7; PinSocket_1x07_P2.54mm_Vertical
U3: 74HCT125; DIP-14_W7.62mm_Socket

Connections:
+3V3: J6.1, R4.1, R6.1, R7.1, U2B.3
+5V: C2.1, C3.1, C4.1, D4.1, J3.1, J4.1, J5.1, J7.1, J8.1, R1.1, U1.3, U2B.1, U3.13, U3.14
AO1: J3.4, R11.1
AO2: J4.4, R12.1
AO3: J5.4, R13.1
BUZ: R5.1, U2B.4
BUZ_N: D4.2, J8.2, Q1.3
CLK5: J7.5, U3.8
CS5: J7.4, U3.6
DIN5: J7.3, U3.3
GAS1: C11.1, R11.2, R21.1, U2A.3
GAS2: C12.1, R12.2, R22.1, U2A.1
GAS3: C13.1, R13.2, R23.1, U2A.2
GND: C1.2, C2.2, C3.2, C4.2, C5.2, C11.2, C12.2, C13.2, D3.2, J1.2, J2.2, J3.2, J4.2, J5.2, J6.2, J7.2, J9.2, LED1.1, Q1.1, Q2.1, R3.2, R21.2, R22.2, R23.2, U1.2, U2B.2, U3.1, U3.4, U3.7, U3.10, U3.12
LED_A: LED1.2, R1.2
MAINS_N: Q2.3, R4.2, U2B.7
MX_CLK: U2B.6, U3.9
MX_CS: U2A.4, U3.5
MX_DIN: U2B.5, U3.2
Q1_B: Q1.2, R5.2
Q2_B: Q2.2, R2.2, R3.1
SCL: J6.4, R7.2, U2A.6
SDA: J6.3, R6.2, U2A.5
SOS: C5.1, J9.1, U2A.7
VIN_BAT: D2.2, J2.1
VIN_MAIN: D1.2, J1.1, R2.1
VPROT: C1.1, D3.1, F1.2, U1.1
VRAIL: D1.1, D2.1, F1.1

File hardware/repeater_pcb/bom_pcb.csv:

Qty,References,Value,Package,Description,Approx price each (INR),Note
1,PCB,MineSafe repeater v4.0,100 x 75 mm 2-layer 1.6 mm,JLCPCB / PCBWay from repeater_gerbers_jlcpcb.zip,60,5 boards ~USD 2 + shipping
1,U1,K7805-2000R3 (or R-78B5.0-2.0),SIP-3,Switching 5 V 2 A regulator 8-32 V in,450,LM7805 + heatsink is NOT a substitute at 24 V (too hot)
2,"D1,D2",1N5822,DO-201AD,3 A Schottky - OR of mine supply and battery,8,
1,D3,P6KE36A,DO-15,36 V TVS surge clamp,10,
1,D4,1N4148,DO-35,Buzzer flyback,1,
1,F1,T1.6A TR5 (Littelfuse 372),TR5,Slow fuse on input,25,
1,C1,470 uF 50 V,radial 10 mm,Input bulk,15,
1,C2,220 uF 16 V,radial 8 mm,5 V bulk,5,
6,"C3,C4,C5,C11,C12,C13",100 nF,disc 5 mm,Decoupling / filter,1,
2,"Q1,Q2",S8050,TO-92,Buzzer driver / mains-present detector,2,
2,"R1,R5",1 k,0.25 W axial,,0.5,
5,"R3,R4,R11,R12,R13",10 k,0.25 W axial,,0.5,
1,R2,22 k,0.25 W axial,,0.5,
3,"R21,R22,R23",20 k,0.25 W axial,MQ divider low side,0.5,
2,"R6,R7",4.7 k,0.25 W axial,I2C pull-ups,0.5,
1,LED1,3 mm green,,Power LED,1,
1,U3,74HCT125,DIP-14 + socket,3.3 V -> 5 V buffer for MAX7219,25,must be HCT not HC
2,"U2A,U2B",1x7 female header 2.54 mm,,Socket for XIAO ESP32-C6,10,
2,"J1,J2",2-pin screw terminal 5.08 mm,MKDS 1.5,Mine supply / battery,12,
4,"J3,J4,J5,J6",JST XH 4-pin + housing + crimps,B4B-XH-A,MQ1-3 / AHT20,6,
1,J7,JST XH 5-pin,B5B-XH-A,MAX7219 matrix,6,
2,"J8,J9",JST XH 2-pin,B2B-XH-A,Buzzer / SOS button,4,
4,H1-H4,M3 x 8 brass standoff + screw,,Board to case bosses (or self-tapping 2.9 x 9),5,

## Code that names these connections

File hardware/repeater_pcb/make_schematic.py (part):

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
    # ---------------- power
    block(30, 100, 640, 470, "Power: mine supply or battery → 5 V (2 A)")
    s.text(50, 140, "J1 MAIN 9–30 V", 12, INK, weight=700); tag(160, 162, "VIN_MAIN"); s.text(50, 166, "pin 1 (+)", 11, MUTED)
    s.text(50, 196, "pin 2 (−)", 11, MUTED); tag(160, 192, "GND")
    s.text(50, 236, "J2 BATT 12 V", 12, INK, weight=700); tag(160, 258, "VIN_BAT"); s.text(50, 262, "pin 1 (+)", 11, MUTED)
    s.text(50, 292, "pin 2 (−)", 11, MUTED); tag(160, 288, "GND")
    # diodes OR
    for i, (net, ref) in enumerate((("VIN_MAIN", "D1"), ("VIN_BAT", "D2"))):
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
    # ---------------- XIAO
    block(720, 100, 520, 470, "Controller: Seeed XIAO ESP32-C6 (on sockets U2A / U2B)")
    left = [("D0 GPIO0", "GAS2"), ("D1 GPIO1", "GAS3"), ("D2 GPIO2", "GAS1"), ("D3 GPIO21", "MX_CS"), ("D4 GPIO22", "SDA"), ("D5 GPIO23", "SCL"), ("D6 GPIO16", "SOS")]
    right = [("5V", "+5V"), ("GND", "GND"), ("3V3", "+3V3"), ("D10 GPIO18", "BUZ"), ("D9 GPIO20", "MX_DIN"), ("D8 GPIO19", "MX_CLK"), ("D7 GPIO17", "MAINS_N")]
    part(880, 150, 200, 200, "", "", left, right)
    s.text(980, 380, "u.FL → pigtail → SMA bulkhead antenna on the case", 11, MUTED, "middle")
    s.text(980, 396, "USB-C (top edge) for programming", 11, MUTED, "middle")
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

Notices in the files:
README.md:
License: MIT
